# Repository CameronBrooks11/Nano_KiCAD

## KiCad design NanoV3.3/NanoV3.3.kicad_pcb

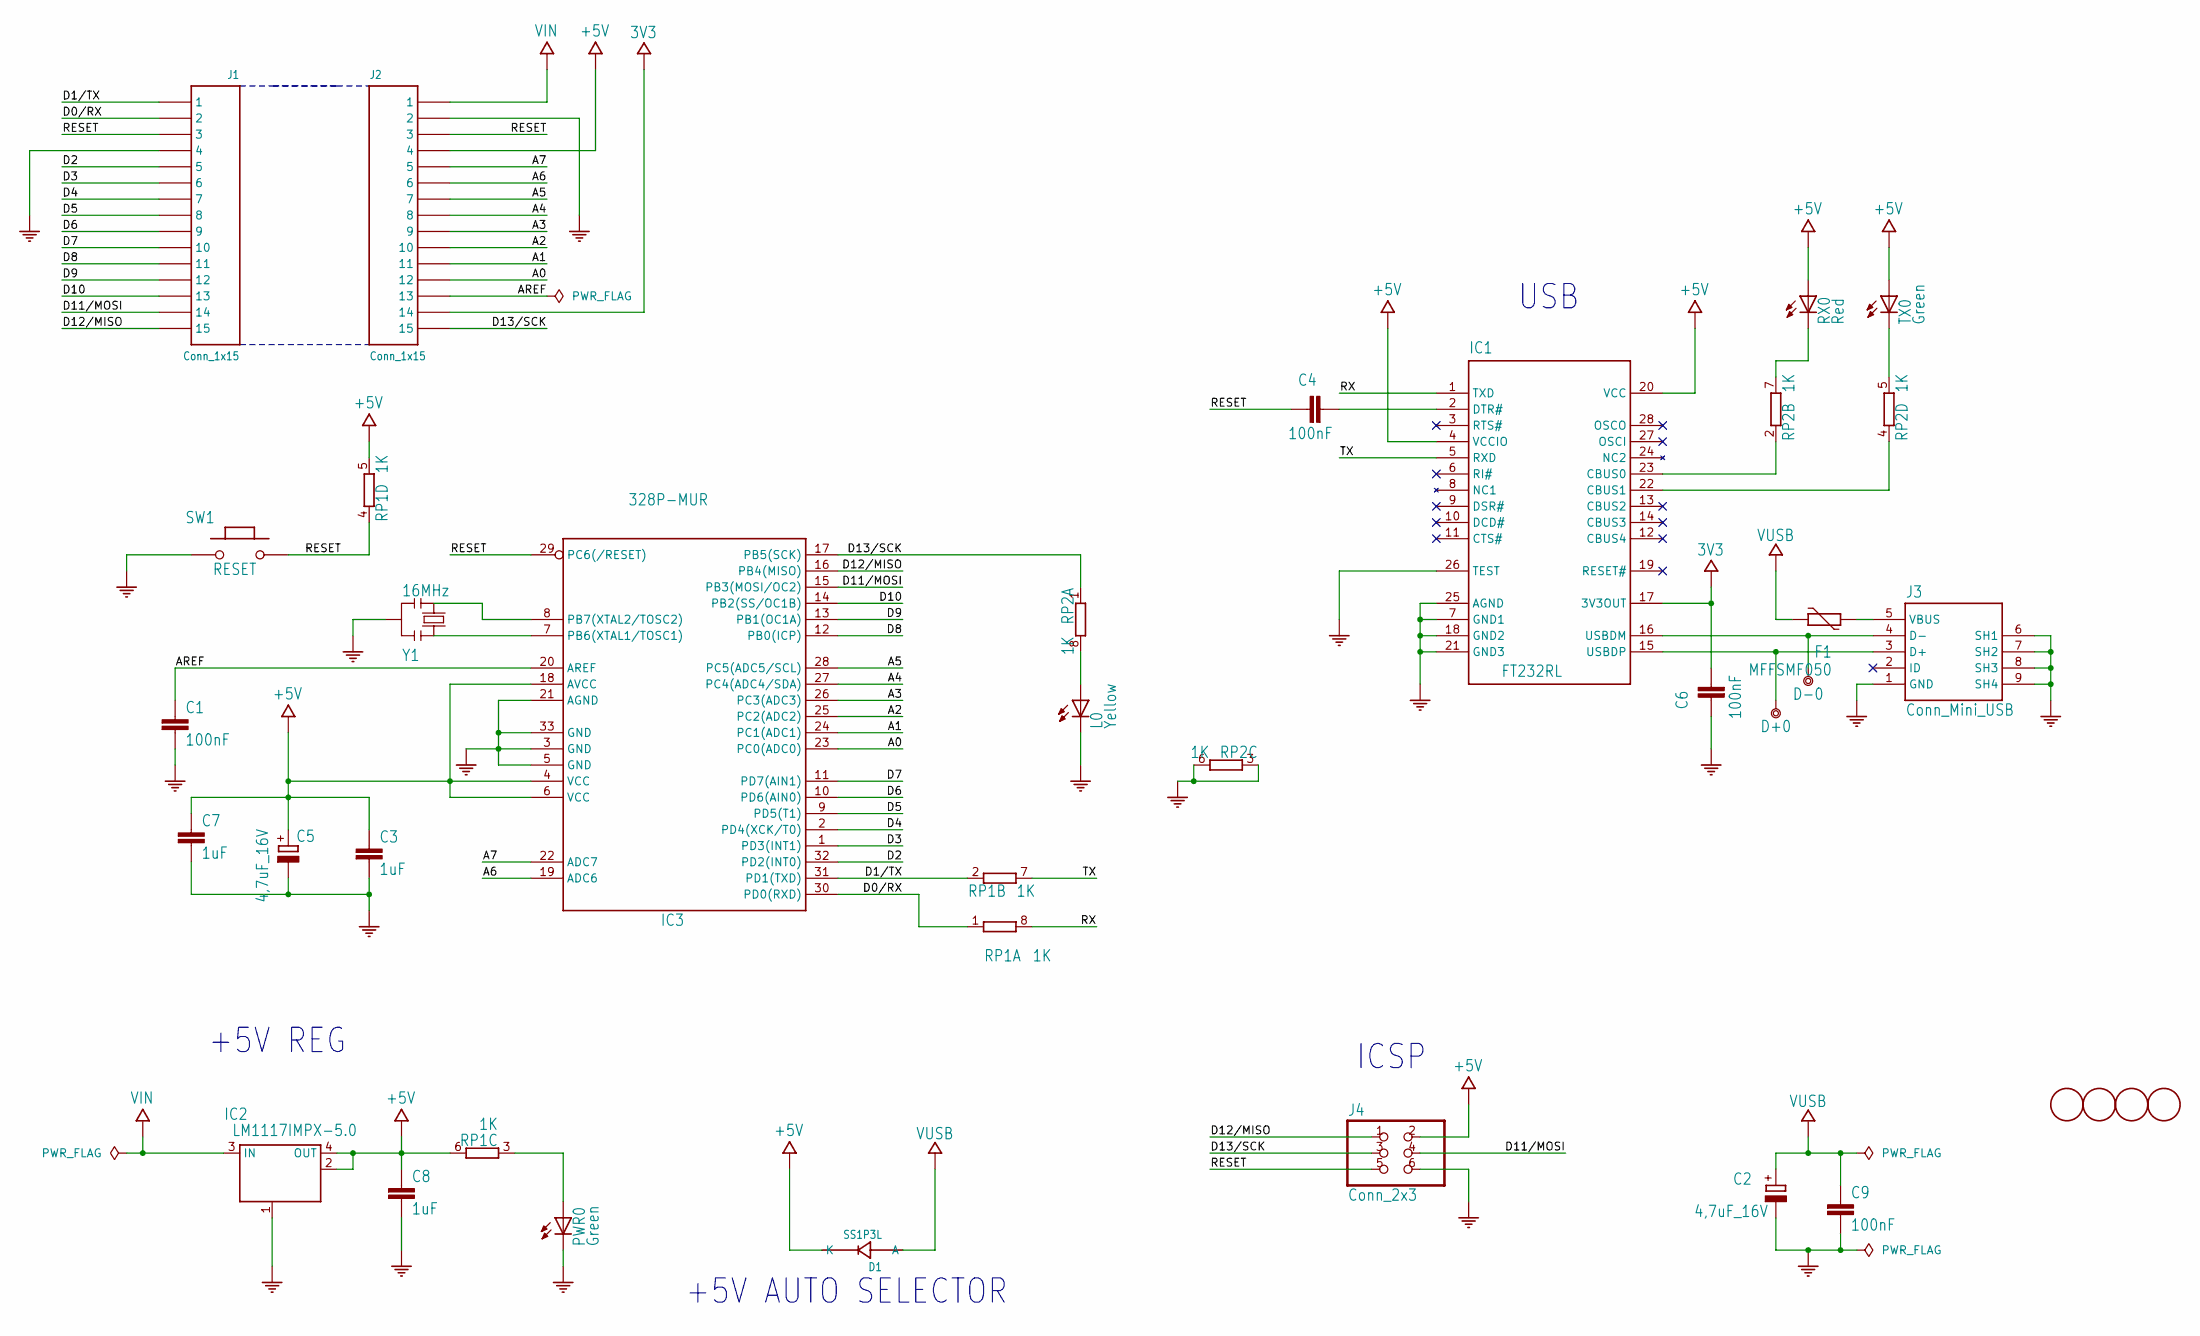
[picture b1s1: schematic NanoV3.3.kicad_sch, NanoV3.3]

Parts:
C1, C4, C6, C9: 100nF; C_0603_1608Metric
C2, C5: 4,7uF_16V; CP_EIA-3216-18_Kemet-A
C3, C7, C8: 1uF; C_0603_1608Metric
D1: SS1P3L; DO-220AA
D+0: DNP; TestPoint_Pad_D1.0mm
D-0: DNP; TestPoint_Pad_D1.0mm
F1: MFFSMF050; Fuse_0603_1608Metric
FD1, FD2, FD3, FD4: DNP; Fiducial_1mm_Mask1.5mm
IC1: FT232RL; SSOP-28_5.3x10.2mm_P0.65mm
IC2: LM1117IMPX-5.0; SOT-223
IC3: 328P-MUR; VQFN-32-1EP_5x5mm_P0.5mm_EP3.254x3.254mm
J1, J2: Conn_1x15; PinHeader_1x15_P2.54mm_Vertical
J3: Conn_Mini_USB; USB_Mini-B_Lumberg_2486_01_Horizontal
J4: Conn_2x3; PinHeader_2x3_P2.54mm_Vertical
L0: Yellow; LED_0805_2012Metric
PWR0: Green; LED_0805_2012Metric
RP1, RP2: 1K; R_CAY16-4
RX0: Red; LED_0805_2012Metric
SW1: RESET; SW_SPST_3.9x2.9mm
TX0: Green; LED_0805_2012Metric
Y1: 16MHz; Resonator_SMD_Murata_CSTxExxV-3Pin_3.0x1.1mm

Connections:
3V3: C6.2, IC1.17 (3V3OUT), J2.14
+5V: C3.1, C5.1 (+), C7.1, C8.1, D1.1 (K), IC1.4 (VCCIO), IC1.20 (VCC), IC2.2, IC2.4 (OUT), IC3.4 (VCC), IC3.6 (VCC), IC3.18 (AVCC), J2.4, J4.2, RP1.5 (2), RP1.6 (2), RX0.1, TX0.1
/A0: IC3.23 (PC0(ADC0)), J2.12
/A1: IC3.24 (PC1(ADC1)), J2.11
/A2: IC3.25 (PC2(ADC2)), J2.10
/A3: IC3.26 (PC3(ADC3)), J2.9
/A4: IC3.27 (PC4(ADC4/SDA)), J2.8
/A5: IC3.28 (PC5(ADC5/SCL)), J2.7
/A6: IC3.19 (ADC6), J2.6
/A7: IC3.22 (ADC7), J2.5
/AREF: C1.1, IC3.20 (AREF), J2.13
/D0/RX: IC3.30 (PD0(RXD)), J1.2, RP1.1
/D1/TX: IC3.31 (PD1(TXD)), J1.1, RP1.2 (1)
/D2: IC3.32 (PD2(INT0)), J1.5
/D3: IC3.1 (PD3(INT1)), J1.6
/D4: IC3.2 (PD4(XCK/T0)), J1.7
/D5: IC3.9 (PD5(T1)), J1.8
/D6: IC3.10 (PD6(AIN0)), J1.9
/D7: IC3.11 (PD7(AIN1)), J1.10
/D8: IC3.12 (PB0(ICP)), J1.11
/D9: IC3.13 (PB1(OC1A)), J1.12
/D10: IC3.14 (PB2(SS/OC1B)), J1.13
/D11/MOSI: IC3.15 (PB3(MOSI/OC2)), J1.14, J4.4
/D12/MISO: IC3.16 (PB4(MISO)), J1.15, J4.1
/D13/SCK: IC3.17 (PB5(SCK)), J2.15, J4.3, RP2.1
/RESET: C4.1, IC3.29 (PC6(/RESET)), J1.3, J2.3, J4.5, RP1.4 (1), SW1.2
/RX: IC1.1 (TXD), RP1.8 (2)
/TX: IC1.5 (RXD), RP1.7 (2)
COM: C1.2, C2.2 (-), C3.2, C5.2 (-), C6.1, C7.2, C8.2, C9.2, IC1.7 (GND1), IC1.18 (GND2), IC1.21 (GND3), IC1.25 (AGND), IC1.26 (TEST), IC2.1 (GND/ADJ), IC3.3 (GND), IC3.5 (GND), IC3.21 (AGND), IC3.33 (GND), J1.4, J2.2, J3.1 (GND), J3.6 (SH1), J3.7 (SH2), J3.8 (SH3), J3.9 (SH4), J4.6, L0.2, PWR0.2, RP2.3 (1), RP2.6 (2), SW1.1, Y1.2
unnamed: C4.2, IC1.2 (DTR#)
unnamed: D+0.X, IC1.15 (USBDP), J3.3 (D+)
unnamed: D-0.X, IC1.16 (USBDM), J3.4 (D-)
unnamed: F1.2, J3.5 (VBUS)
unnamed: IC1.22 (CBUS1), RP2.4 (1)
unnamed: IC1.23 (CBUS0), RP2.2 (1)
unnamed: IC3.7 (PB6(XTAL1/TOSC1)), Y1.1
unnamed: IC3.8 (PB7(XTAL2/TOSC2)), Y1.3
unnamed: L0.1, RP2.8 (2)
unnamed: PWR0.1, RP1.3 (1)
unnamed: RP2.5 (2), TX0.2
unnamed: RP2.7 (2), RX0.2
VIN: IC2.3 (IN), J2.1
VUSB: C2.1 (+), C9.1, D1.2 (A), F1.1

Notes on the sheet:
+5V REG
+5V AUTO SELECTOR
ICSP
USB

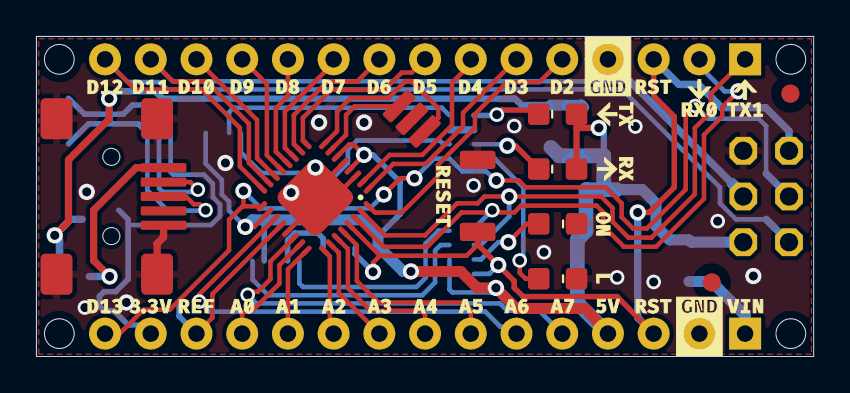
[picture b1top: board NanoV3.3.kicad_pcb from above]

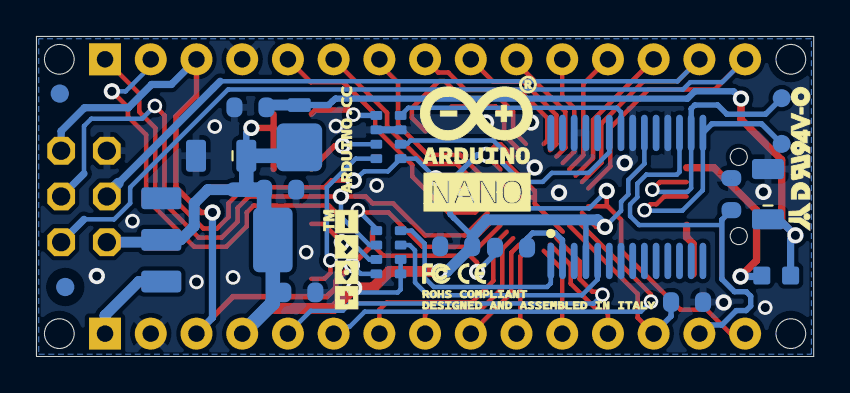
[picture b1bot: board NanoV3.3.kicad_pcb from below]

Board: 2 copper layers, 43.2 x 17.8 mm, 34 parts (20 on the bottom side), 43 nets.

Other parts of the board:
Silkscreen_Back: Silkscreen_Front; Silkscreen_Back
Silkscreen_Front: Silkscreen_Back; Silkscreen_Front

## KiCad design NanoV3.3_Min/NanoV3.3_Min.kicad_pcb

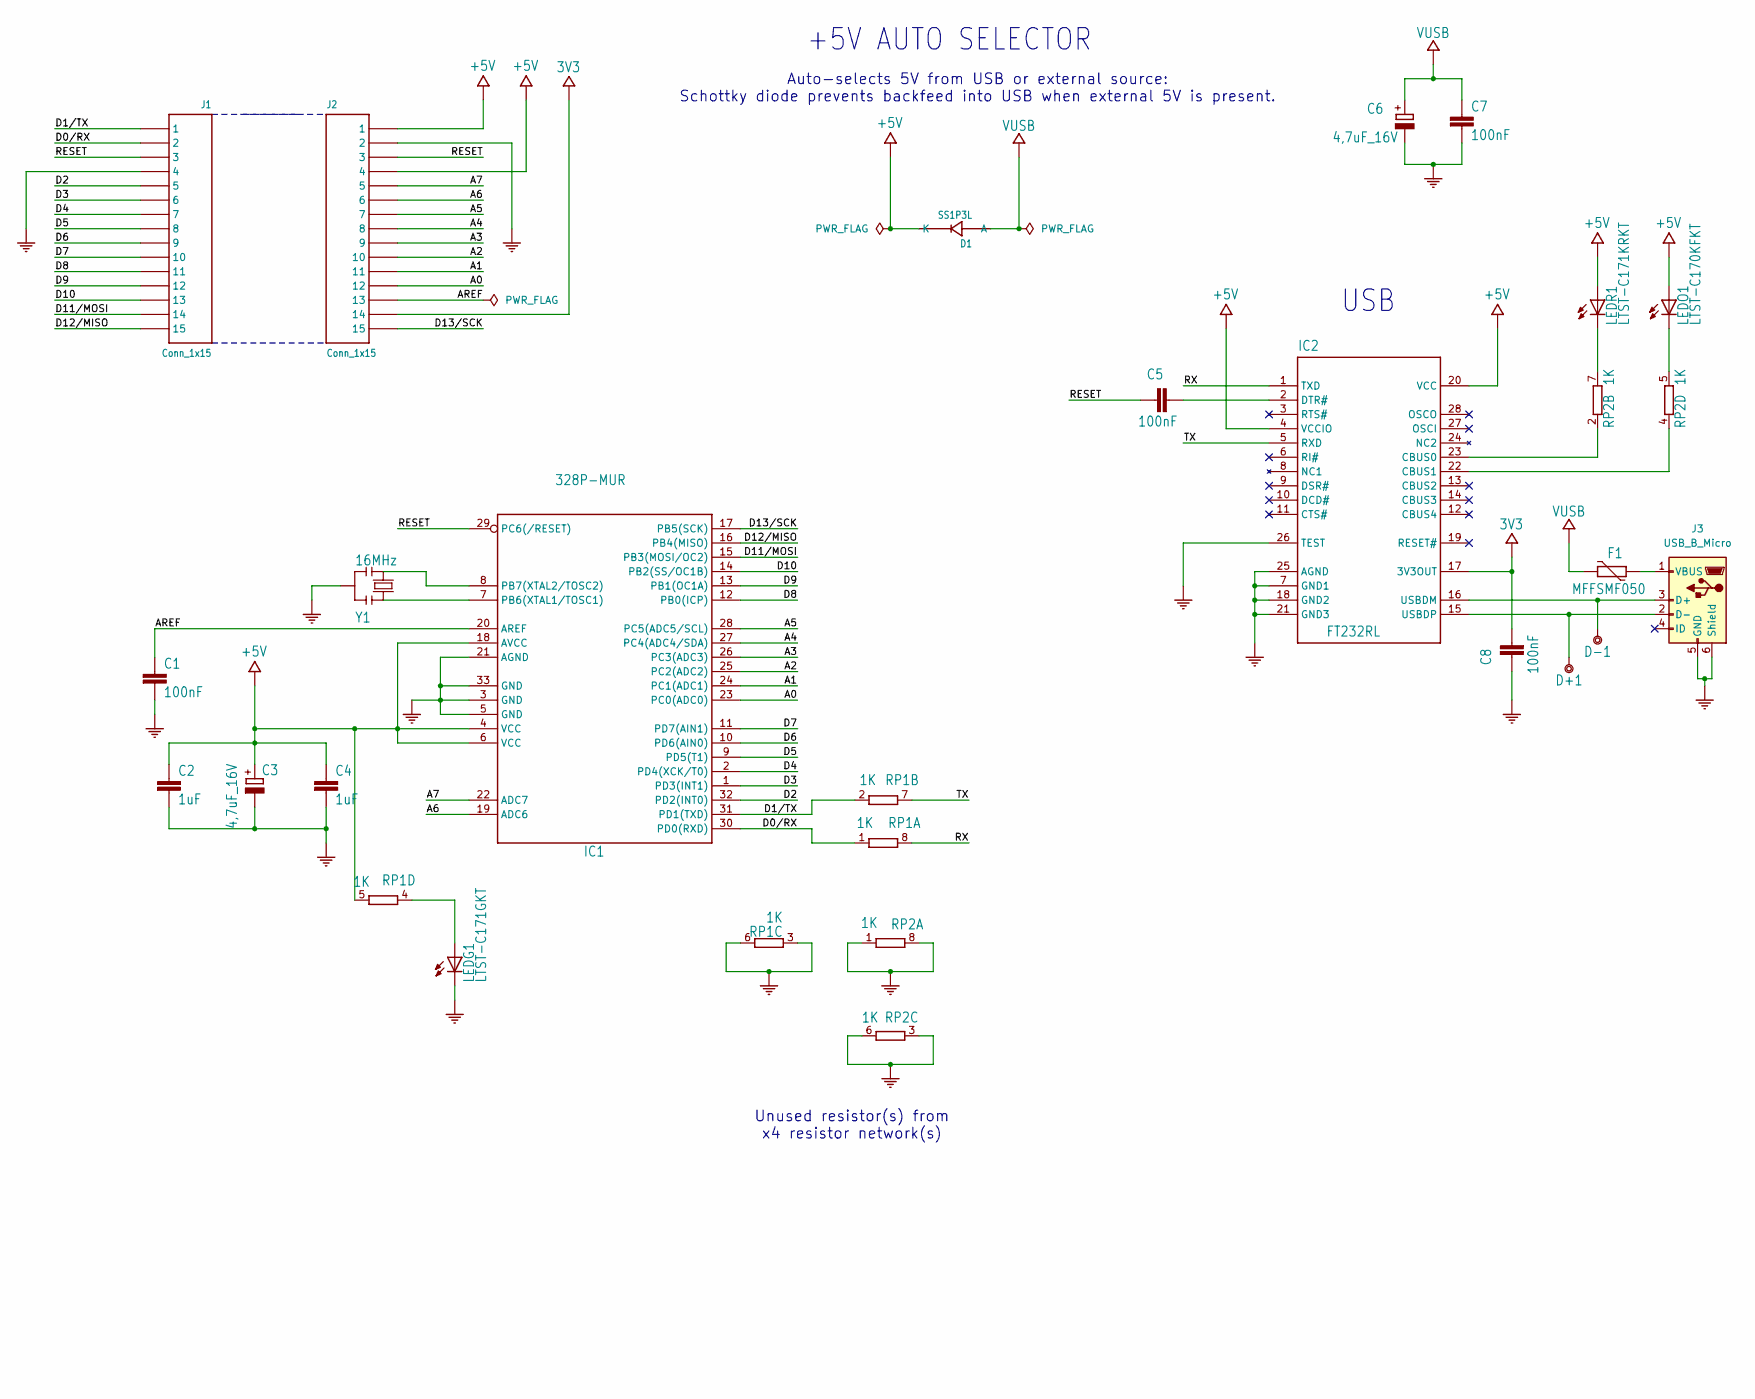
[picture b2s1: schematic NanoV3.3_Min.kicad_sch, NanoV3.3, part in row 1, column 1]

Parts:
C1, C5, C7, C8: 100nF; C_0603_1608Metric
C2, C4: 1uF; C_0603_1608Metric
C3, C6: 4,7uF_16V; CP_EIA-3216-18_Kemet-A
D1: SS1P3L; DO-220AA
D6: LED
D+1: DNP; TestPoint_Pad_D1.0mm
D-1: DNP; TestPoint_Pad_D1.0mm
F1: MFFSMF050; Fuse_0603_1608Metric
IC1: 328P-MUR; VQFN-32-1EP_5x5mm_P0.5mm_EP3.254x3.254mm
IC2: FT232RL; SSOP-28_5.3x10.2mm_P0.65mm
J1, J2: Conn_1x15; PinHeader_1x15_P2.54mm_Vertical
J3: USB_B_Micro; USB_Micro-B_Amphenol_10118193-0001LF_Horizontal
LEDG1: LTST-C171GKT; LED_0805_2012Metric
LEDO1: LTST-C170KFKT; LED_0805_2012Metric
LEDR1: LTST-C171KRKT; LED_0805_2012Metric
RP1, RP2: 1K; R_CAY16-4
Y1: 16MHz; Resonator_SMD_Murata_CSTxExxV-3Pin_3.0x1.1mm

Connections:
3V3: C8.2, IC2.17 (3V3OUT), J2.14
+5V: C2.1, C3.1 (+), C4.1, D1.1 (K), IC1.4 (VCC), IC1.6 (VCC), IC1.18 (AVCC), IC2.4 (VCCIO), IC2.20 (VCC), J2.1, J2.4, LEDO1.1, LEDR1.1, RP1.5 (2)
/A0: IC1.23 (PC0(ADC0)), J2.12
/A1: IC1.24 (PC1(ADC1)), J2.11
/A2: IC1.25 (PC2(ADC2)), J2.10
/A3: IC1.26 (PC3(ADC3)), J2.9
/A4: IC1.27 (PC4(ADC4/SDA)), J2.8
/A5: IC1.28 (PC5(ADC5/SCL)), J2.7
/A6: IC1.19 (ADC6), J2.6
/A7: IC1.22 (ADC7), J2.5
/AREF: C1.1, IC1.20 (AREF), J2.13
/D0/RX: IC1.30 (PD0(RXD)), J1.2, RP1.1
/D1/TX: IC1.31 (PD1(TXD)), J1.1, RP1.2 (1)
/D2: IC1.32 (PD2(INT0)), J1.5
/D3: IC1.1 (PD3(INT1)), J1.6
/D4: IC1.2 (PD4(XCK/T0)), J1.7
/D5: IC1.9 (PD5(T1)), J1.8
/D6: IC1.10 (PD6(AIN0)), J1.9
/D7: IC1.11 (PD7(AIN1)), J1.10
/D8: IC1.12 (PB0(ICP)), J1.11
/D9: IC1.13 (PB1(OC1A)), J1.12
/D10: IC1.14 (PB2(SS/OC1B)), J1.13
/D11/MOSI: IC1.15 (PB3(MOSI/OC2)), J1.14
/D12/MISO: IC1.16 (PB4(MISO)), J1.15
/D13/SCK: IC1.17 (PB5(SCK)), J2.15
/RESET: C5.1, IC1.29 (PC6(/RESET)), J1.3, J2.3
/RX: IC2.1 (TXD), RP1.8 (2)
/TX: IC2.5 (RXD), RP1.7 (2)
COM: C1.2, C2.2, C3.2 (-), C4.2, C6.2 (-), C7.2, C8.1, IC1.3 (GND), IC1.5 (GND), IC1.21 (AGND), IC1.33 (GND), IC2.7 (GND1), IC2.18 (GND2), IC2.21 (GND3), IC2.25 (AGND), IC2.26 (TEST), J1.4, J2.2, J3.5 (GND), J3.6 (Shield), LEDG1.2, RP1.3 (1), RP1.6 (2), RP2.1, RP2.3 (1), RP2.6 (2), RP2.8 (2), Y1.2
unnamed: D+1.X, IC2.15 (USBDP), J3.2 (D-)
unnamed: D-1.X, IC2.16 (USBDM), J3.3 (D+)
unnamed: IC1.7 (PB6(XTAL1/TOSC1)), Y1.1
unnamed: IC1.8 (PB7(XTAL2/TOSC2)), Y1.3
unnamed: IC2.23 (CBUS0), RP2.2 (1)
unnamed: IC2.22 (CBUS1), RP2.4 (1)
unnamed: C5.2, IC2.2 (DTR#)
unnamed: F1.2, J3.1 (VBUS)
unnamed: LEDG1.1, RP1.4 (1)
unnamed: LEDR1.2, RP2.7 (2)
unnamed: LEDO1.2, RP2.5 (2)
VUSB: C6.1 (+), C7.1, D1.2 (A), F1.1

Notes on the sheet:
+5V AUTO SELECTOR
USB
Auto-selects 5V from USB or external source: Schottky diode prevents backfeed into USB when external 5V is present.
Unused resistor(s) from x4 resistor network(s)

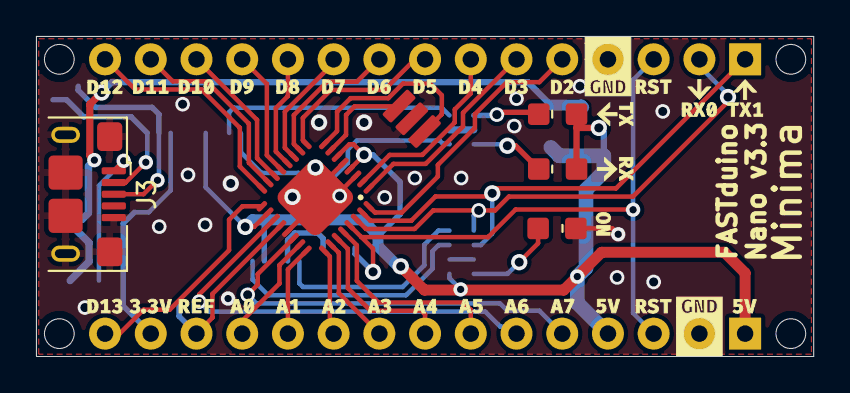
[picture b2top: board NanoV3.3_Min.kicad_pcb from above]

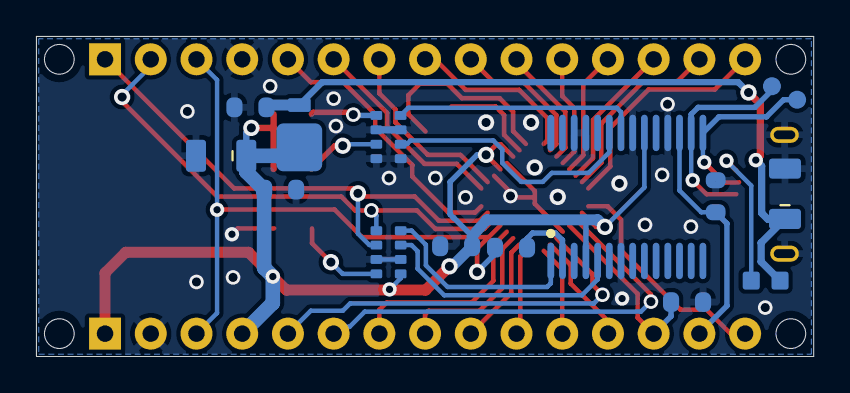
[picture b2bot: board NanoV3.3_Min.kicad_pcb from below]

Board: 2 copper layers, 43.2 x 17.8 mm, 24 parts (15 on the bottom side), 41 nets.

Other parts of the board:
Silkscreen_Front: Silkscreen_Back; Silkscreen_Front

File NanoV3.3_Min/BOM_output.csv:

"Reference","Value","Footprint","Datasheet","Qty","DNP"
"C1,C5,C7,C8","100nF","NanoV3.3:C_0603_1608Metric","","4",""
"C2,C4","1uF","NanoV3.3:C_0603_1608Metric","","2",""
"C3,C6","4,7uF_16V","NanoV3.3:CP_EIA-3216-18_Kemet-A","","2",""
"D+1,D-1","DNP","NanoV3.3:TestPoint_Pad_D1.0mm","","2",""
"D1","SS1P3L","NanoV3.3:DO-220AA","","1",""
"F1","MFFSMF050","NanoV3.3:Fuse_0603_1608Metric","","1",""
"IC1","328P-MUR","NanoV3.3:VQFN-32-1EP_5x5mm_P0.5mm_EP3.254x3.254mm","","1",""
"IC2","FT232RL","NanoV3.3:SSOP-28_5.3x10.2mm_P0.65mm","","1",""
"J1,J2","Conn_1x15","NanoV3.3:PinHeader_1x15_P2.54mm_Vertical","","2",""
"J3","USB_B_Micro","Connector_USB:USB_Micro-B_Amphenol_10118193-0001LF_Horizontal","~","1",""
"LEDG1","LTST-C171GKT","NanoV3.3:LED_0805_2012Metric","","1",""
"LEDO1","LTST-C170KFKT","NanoV3.3:LED_0805_2012Metric","","1",""
"LEDR1","LTST-C171KRKT","NanoV3.3:LED_0805_2012Metric","","1",""
"RP1,RP2","1K","NanoV3.3:R_CAY16-4","","2",""
"Y1","16MHz","NanoV3.3:Resonator_SMD_Murata_CSTxExxV-3Pin_3.0x1.1mm","","1",""

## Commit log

2025-03-26 added minimal version
2025-03-28 finalized first iteration of nano minima
2025-03-30 added docs folder with readme to take notes
2025-04-19 minor tweaks
2025-04-21 added bom start
